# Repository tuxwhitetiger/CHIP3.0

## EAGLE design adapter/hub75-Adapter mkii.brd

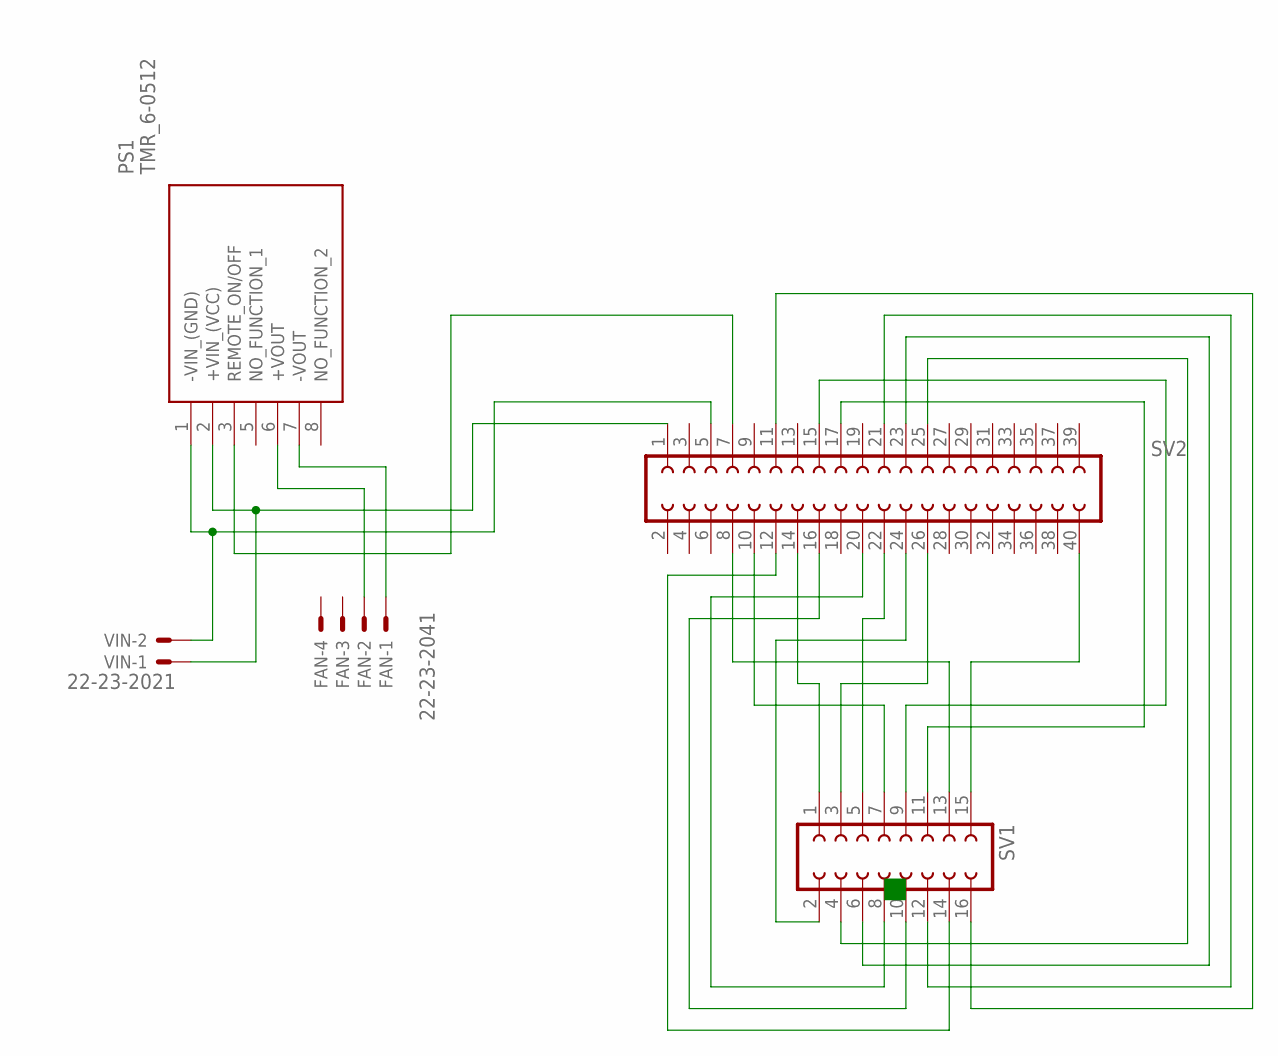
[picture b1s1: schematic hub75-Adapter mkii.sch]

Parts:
FAN: 22-23-2041
PS1: TMR_6-0512; TMR-6
SV1: FE08-2
SV2: FE20-2
VIN: 22-23-2021

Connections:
unnamed: SV1.1, SV2.14
unnamed: SV1.3, SV2.26
unnamed: SV1.5, SV2.22
unnamed: SV1.7, SV2.10
unnamed: SV1.9, SV2.15
unnamed: SV1.11, SV2.17
unnamed: SV1.13, SV2.8
unnamed: SV1.15, SV2.40
unnamed: SV1.2, SV2.24
unnamed: SV1.4, SV2.25
unnamed: SV1.6, SV2.23
unnamed: SV1.8, SV2.20
unnamed: SV1.10, SV2.16
unnamed: PS1.3 (REMOTE_ON/OFF), SV2.7
unnamed: SV1.12, SV2.21
unnamed: SV1.14, SV2.12
unnamed: PS1.2 (+VIN_(VCC)), SV2.1, VIN.1
unnamed: FAN.1, PS1.7 (-VOUT)
unnamed: SV1.16, SV2.11
unnamed: FAN.2, PS1.6 (+VOUT)
unnamed: PS1.1 (-VIN_(GND)), SV2.5, VIN.2

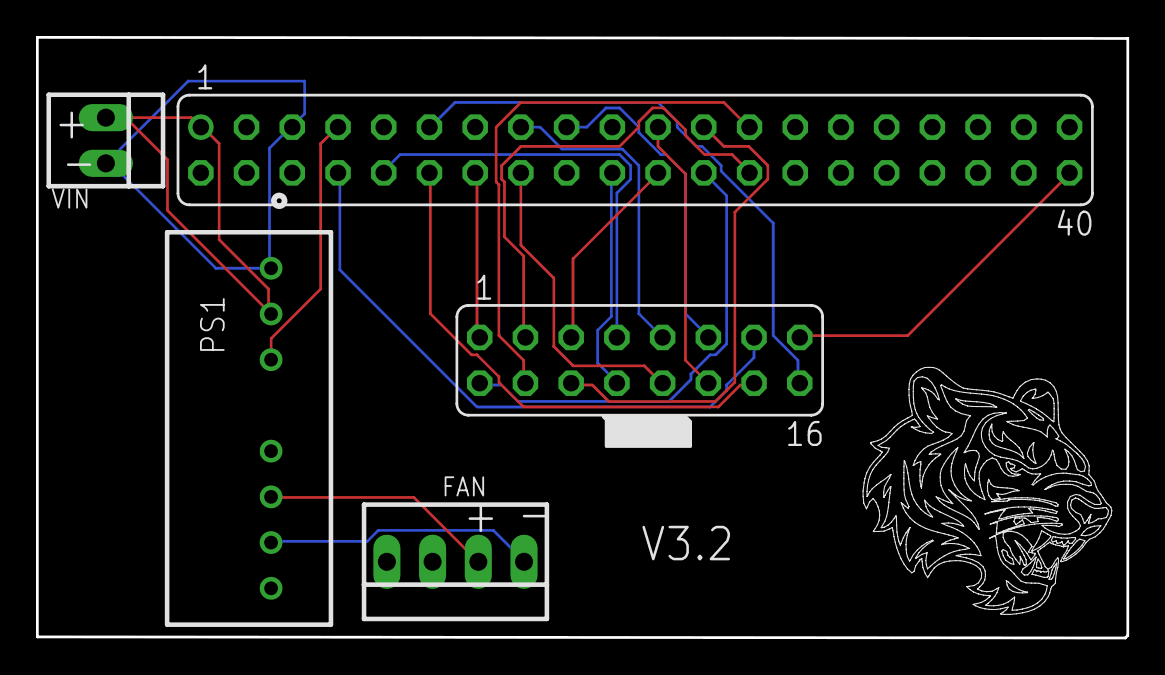
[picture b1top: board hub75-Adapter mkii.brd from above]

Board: 2 copper layers, 60.6 x 33.4 mm, 5 parts (0 on the bottom side), 21 nets.

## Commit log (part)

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2023-11-25 add webserver test
2023-11-30 addd bat handeler to web
2024-01-04 more
2024-01-14 firewall fix
2024-02-13 built from laptop
2024-02-13 from laptop
2026-04-26 Revert ".."
    This reverts commit 9a37da02bcd21a9e83090db3705bd8ad125f65a8.
2026-04-26 Revert ".."
    This reverts commit 8a51c526afa631d91a826389a319780528afaee1.
2026-04-26 Revert ".."
    This reverts commit 8632df42c252d7f0ec17bfa3a3c75f4fc91a42e8, reversing
    changes made to 6906d5598f6e305d42e19ad3035f708972749f4e.
2026-04-26 Revert ".."
    This reverts commit 6906d5598f6e305d42e19ad3035f708972749f4e.
2026-04-26 Revert ".."
    This reverts commit 47166482147d34ca53013a8bc70c00775f91e183.
2026-04-26 Revert ".."
    This reverts commit c578c08a575c15177594febcb670ca7df9233633.
2026-04-26 built from stormrage
